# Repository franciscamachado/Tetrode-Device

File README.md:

# Tetrode-Device

We have developed a simple and affordable tetrode-based device that allows interchangeable extracellular recordings of neural activity between in vivo and ex vivo preparations and can be easily implemented in all wet-bench laboratories.

## Building Instructions
Construction and usage are described in the [paper](https://www.sciencedirect.com/science/article/pii/S0165027020301783).

**Assembly Parts:**

**(1) - Electrode Interface Board (EIB).** The EIB's gerber files are provided in the "Design" folder for three different headstages: (1) RHD32 (Intan/Open Ephys) ([link](https://github.com/franciscamachado/Tetrode-Device/tree/master/Designs/EIB/Eagle/OpenEphys)), (2) HS-36-LED (NeuraLynx) ([link](https://github.com/franciscamachado/Tetrode-Device/tree/master/Designs/EIB/Eagle/Neuralynx)) and (3) HST/32D Plexon ([link](https://github.com/franciscamachado/Tetrode-Device/tree/master/Designs/EIB/Eagle/Plexon)). Each EIB is provided intwo versions: the first with independent GND and REF and the second with shorted GND and REF. The EIB should be manufactured with electroless nickel immersion gold (ENIG) surface finishing.

**(2) - A79024-001 Omnetics connector** ([link](https://www.omnetics.com/products/neuro-connectors/nano-strip-connectors)). 

**(3) - Small gold pins** ([link](https://neuralynx.com/hardware/small-eib-pins)). 

**(4) - Tetrode guide.** The .STL files of the tetrode guide are available with 2 single track widths: 0.3 mm ([link](https://github.com/franciscamachado/Tetrode-Device/blob/master/Designs/Tetrode%20Guide/0.3mmTrack.stl)) and 0.6 mm ([link](https://github.com/franciscamachado/Tetrode-Device/blob/master/Designs/Tetrode%20Guide/0.6mmTrack.stl)). An .STL file for the tetrode guide with an optogenetic extention is also available ([link](https://github.com/franciscamachado/Tetrode-Device/tree/master/Designs/Tetrode%20Guide/Optogenetic%20Extension)). These designs are easily altered and adjusted to the size and number of tetrodes to be used.

**(5) - Tetrode wire** (depending on application).

## Citing this Work

When using this device, please cite the paper:

Francisca Machado, Nuno Sousa, Patricia Monteiro, Luis Jacinto (2020). A versatile and modular tetrode-based device for single-unit recordings in rodent ex vivo and in vivo acute preparations. J Neurosci Methods, 341:108755. [Link](https://www.sciencedirect.com/science/article/pii/S0165027020301783)

## License

<br />This work is licensed with a License <a rel="license" href="http://creativecommons.org/licenses/by-nc/4.0/">Creative Commons - Attribution-NonCommercial 4.0 International</a>.

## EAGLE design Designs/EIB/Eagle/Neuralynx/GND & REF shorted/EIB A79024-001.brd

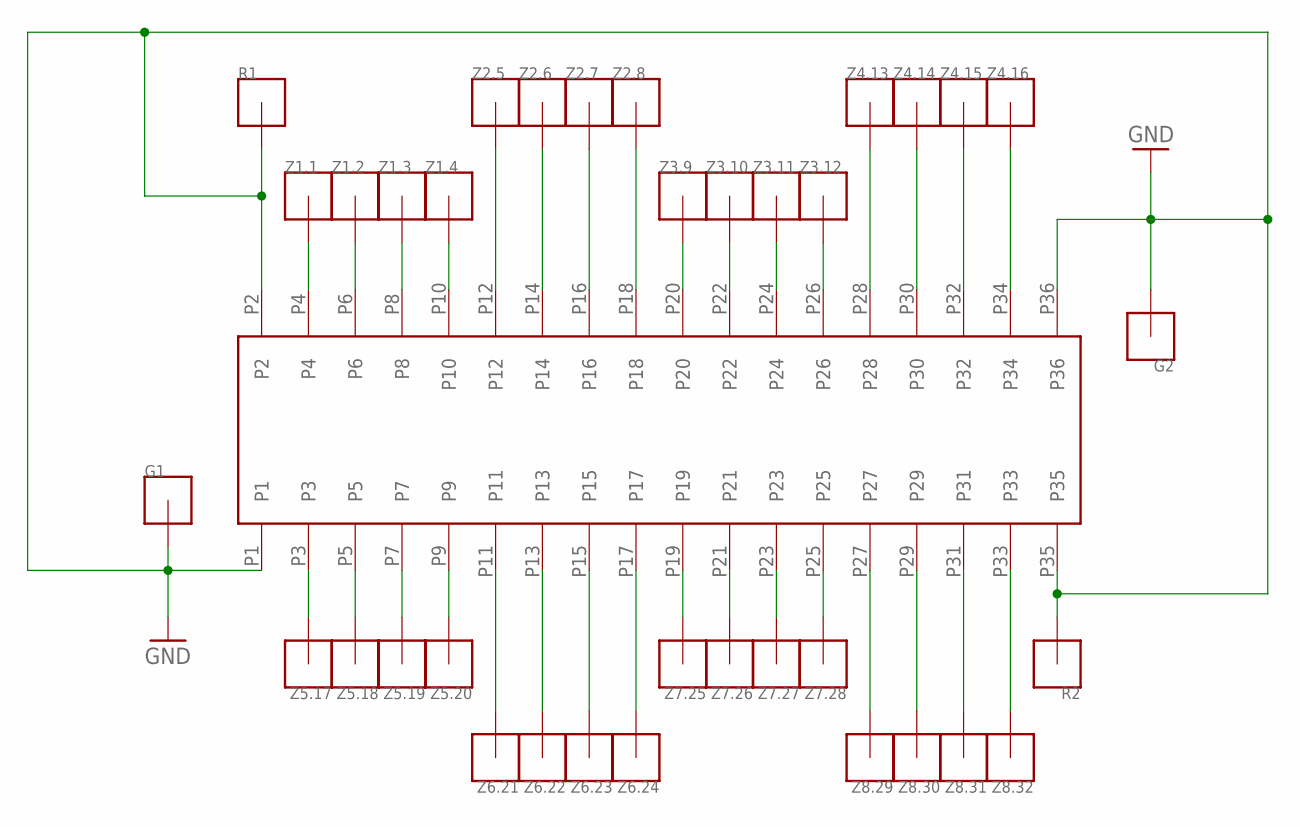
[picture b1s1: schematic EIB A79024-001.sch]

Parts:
A79024: OMNETICS; A79024
G1, G2: S_P_HOLE
R1, R2: S_P_HOLE
Z1.1, Z1.2, Z1.3, Z1.4, Z2.5, Z2.6, Z2.7, Z2.8, Z3.9, Z3.10, Z3.11, Z3.12, Z4.13, Z4.14, Z4.15, Z4.16, Z5.17, Z5.18, Z5.19, Z5.20, Z6.21, Z6.22, Z6.23, Z6.24, Z7.25, Z7.26, Z7.27, Z7.28, Z8.29, Z8.30, Z8.31, Z8.32: S_P_HOLE

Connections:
GND: A79024.P1, A79024.P2, A79024.P35, A79024.P36, G1.P1, G2.P1, R1.P1, R2.P1
unnamed: A79024.P4, Z1.1.P1
unnamed: A79024.P6, Z1.2.P1
unnamed: A79024.P8, Z1.3.P1
unnamed: A79024.P10, Z1.4.P1
unnamed: A79024.P12, Z2.5.P1
unnamed: A79024.P14, Z2.6.P1
unnamed: A79024.P16, Z2.7.P1
unnamed: A79024.P18, Z2.8.P1
unnamed: A79024.P20, Z3.9.P1
unnamed: A79024.P22, Z3.10.P1
unnamed: A79024.P24, Z3.11.P1
unnamed: A79024.P26, Z3.12.P1
unnamed: A79024.P28, Z4.13.P1
unnamed: A79024.P30, Z4.14.P1
unnamed: A79024.P32, Z4.15.P1
unnamed: A79024.P34, Z4.16.P1
unnamed: A79024.P33, Z8.32.P1
unnamed: A79024.P31, Z8.31.P1
unnamed: A79024.P29, Z8.30.P1
unnamed: A79024.P27, Z8.29.P1
unnamed: A79024.P25, Z7.28.P1
unnamed: A79024.P23, Z7.27.P1
unnamed: A79024.P21, Z7.26.P1
unnamed: A79024.P19, Z7.25.P1
unnamed: A79024.P17, Z6.24.P1
unnamed: A79024.P15, Z6.23.P1
unnamed: A79024.P13, Z6.22.P1
unnamed: A79024.P11, Z6.21.P1
unnamed: A79024.P9, Z5.20.P1
unnamed: A79024.P7, Z5.19.P1
unnamed: A79024.P5, Z5.18.P1
unnamed: A79024.P3, Z5.17.P1

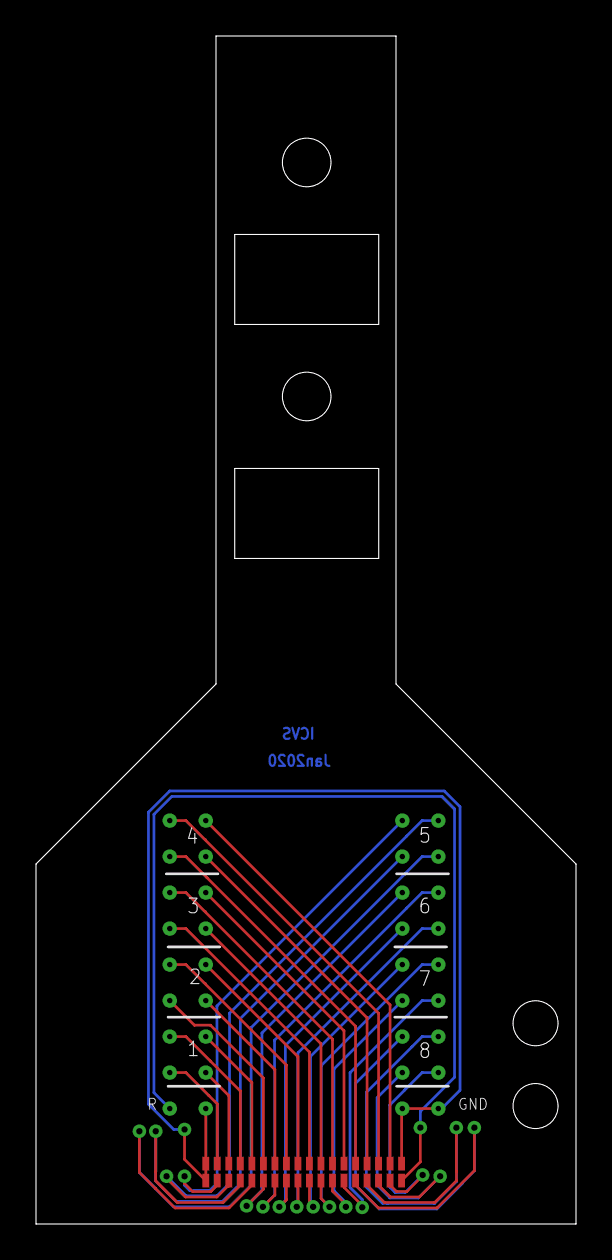
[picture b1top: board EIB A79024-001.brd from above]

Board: 2 copper layers, 30.0 x 66.0 mm, 37 parts (0 on the bottom side), 33 nets.
